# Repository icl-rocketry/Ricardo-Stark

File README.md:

# Ricardo-Stark (Engine Control Unit)

An integrated engine control unit designed to fire and control liquid bi-propellant rocket engines. Stark v1.0 has been tested in several cold flows and hotfire tests for engines ranging from 500N to 5kN. It has been flight tested on Nimbus 24 (ICLR's first liquid rocket launch) at the European Rocketry Challenge '24.

## Hardware (v1.0)
- ESP32-S3 microcontroller
- x2 Servo Channels with voltage monitor
- x1 Pyro Channel with regulated 12V
- x6 24 bit ADC channels
- microSD card logging
- x4 GPIO breakout
- CAN Bus
- USB-C Port

## Software (v1.0)
- Finite State Machine implementation
- Custom ignition sequence with propellant feed delay
- Custom valve angle configuration
- Optional remote configurability to ignition sequence

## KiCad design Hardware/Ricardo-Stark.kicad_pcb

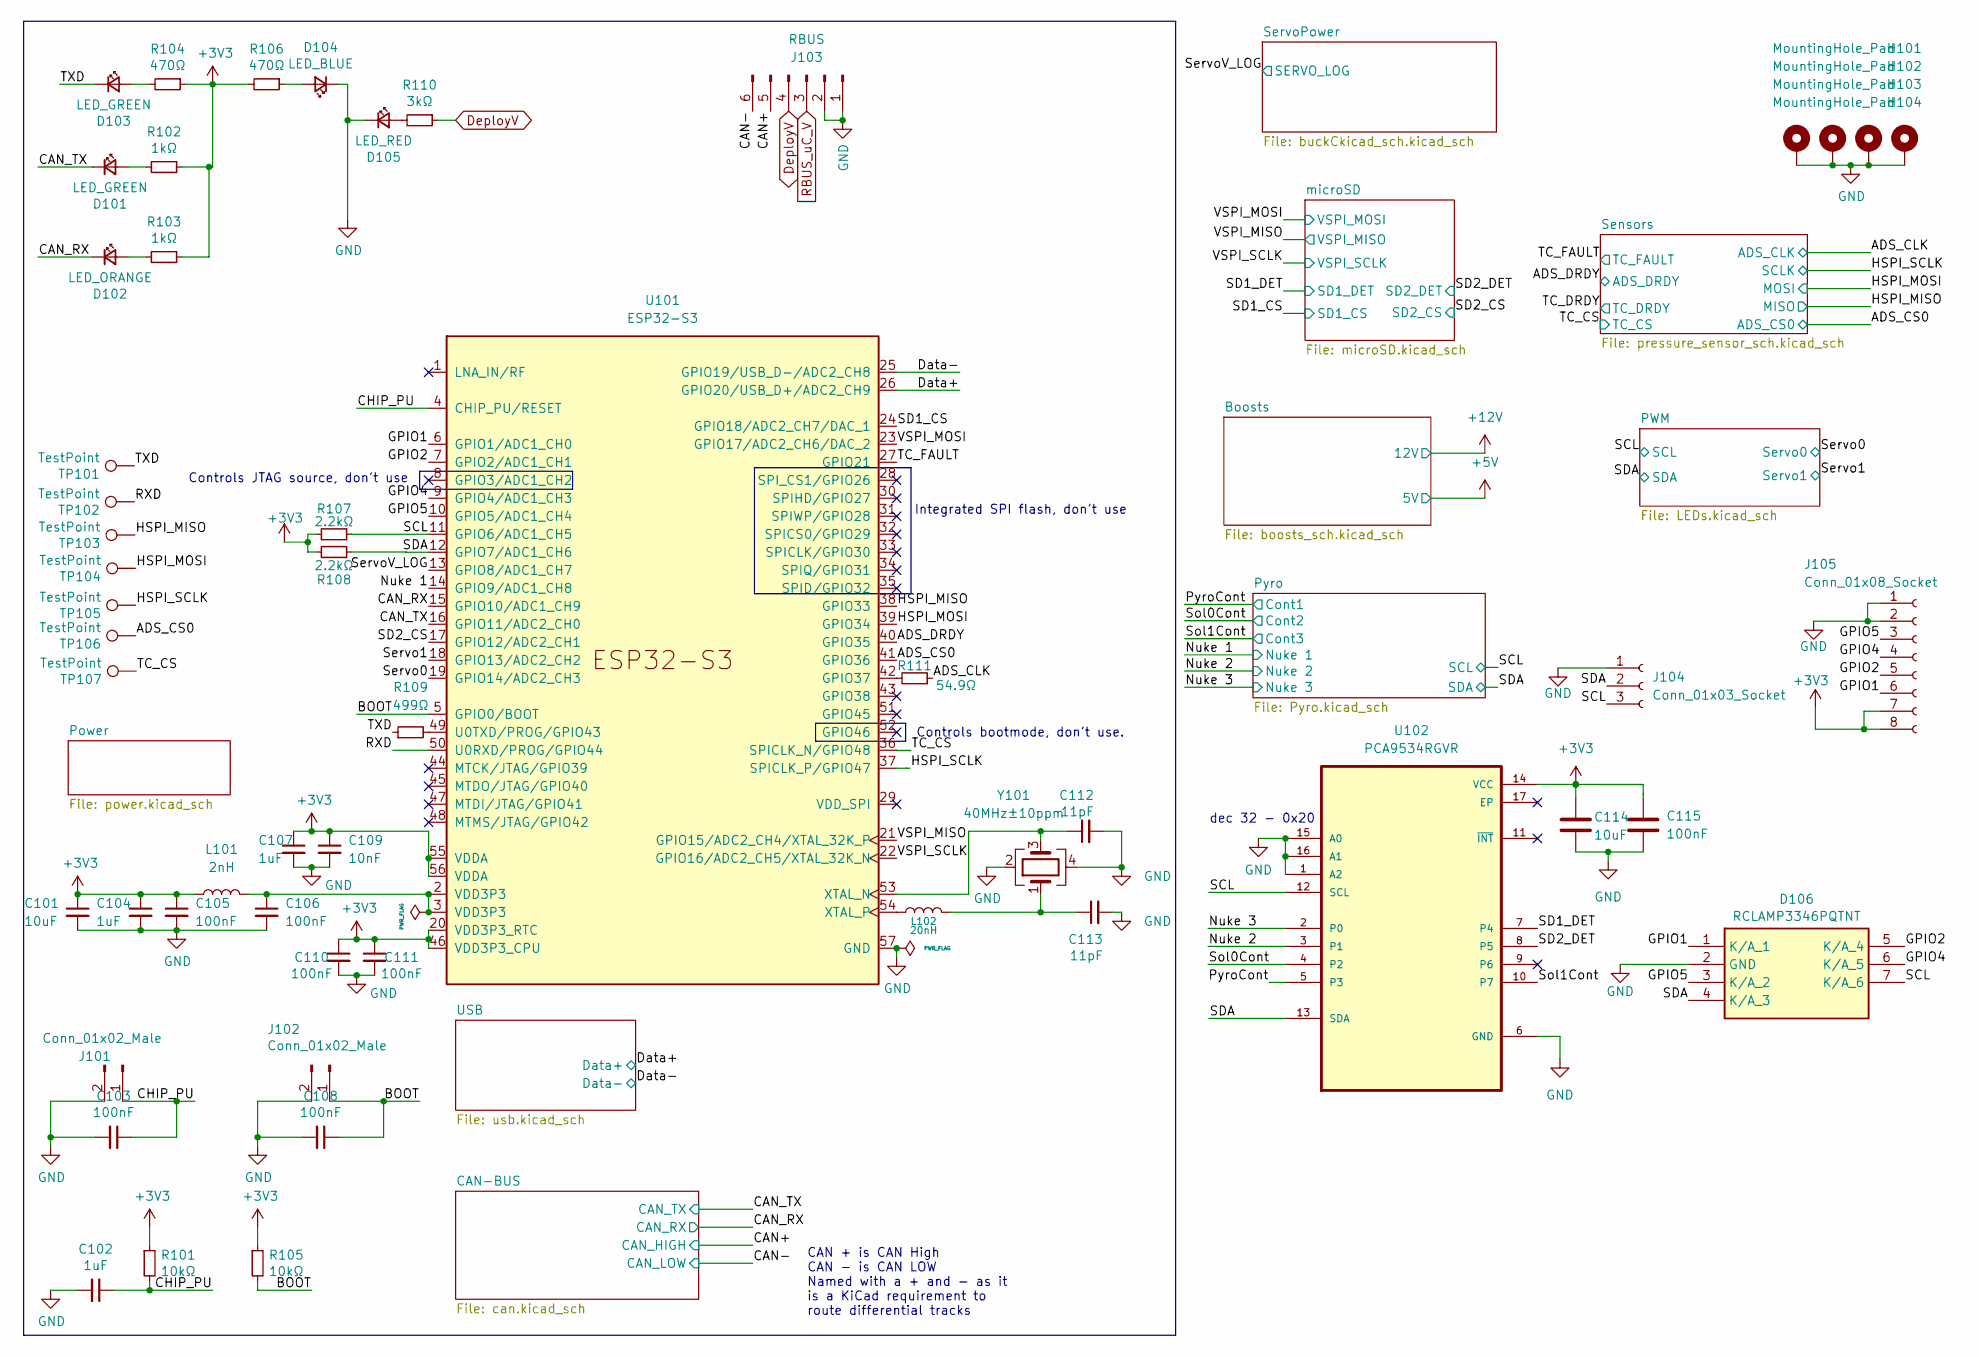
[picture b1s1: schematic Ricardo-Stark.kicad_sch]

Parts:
C101, C114: 10uF; C_0402_1005Metric
C102, C104, C107: 1uF; C_0402_1005Metric
C103, C105, C106, C108, C110, C111, C115: 100nF; C_0402_1005Metric
C109: 10nF; C_0402_1005Metric
C112, C113: 11pF; C_0402_1005Metric
D101, D103: LED_GREEN; LED_0402_1005Metric
D102: LED_ORANGE; LED_0402_1005Metric
D104: LED_BLUE; LED_0402_1005Metric
D105: LED_RED; LED_0402_1005Metric
D106: RCLAMP3346PQTNT; Mouser Part Number 947-RCLAMP3346PQTNT
H101, H102, H103, H104: MountingHole_Pad; MountingHole_3.2mm_M3_DIN965_Pad
J101, J102: Conn_01x02_Male; PinHeader_1x02_P2.54mm_Vertical
J103: RBUS; Molex_Mini-Fit_Jr_5569-06A2_2x03_P4.20mm_Horizontal
J104: Conn_01x03_Socket; PinHeader_1x03_P2.54mm_Vertical
J105: Conn_01x08_Socket; PinHeader_2x04_P2.54mm_Vertical
L101: 2nH; L_0402_1005Metric
L102: 20nH; L_0402_1005Metric
R101, R105: 10kΩ; R_0402_1005Metric
R102, R103: 1kΩ; R_0402_1005Metric
R104, R106: 470Ω; R_0402_1005Metric
R107, R108: 2.2kΩ; R_0402_1005Metric
R109: 499Ω; R_0402_1005Metric
R110: 3kΩ; R_0402_1005Metric
R111: 54.9Ω; R_0402_1005Metric
TP101, TP102, TP103, TP104, TP105, TP106, TP107: TestPoint; TestPoint_Pad_D1.0mm
U101: ESP32-S3; QFN40P700X700X90-57N
U102: PCA9534RGVR; QFN65P400X400X100-17N
Y101: 40MHz±10ppm; Crystal_SMD_2016-4Pin_2.0x1.6mm; MPN R940000171

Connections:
+3.3V: C101.1, C104.1, C105.1, C107.1, C109.1, C110.1, C111.1, C114.1, C115.1, J105.7, J105.8, L101.1, R101.1, R102.1, R103.1, R104.1, R105.1, R106.2, R107.2, R108.2, U101.20 (VDD3P3_RTC), U101.46 (VDD3P3_CPU), U101.55 (VDDA), U101.56 (VDDA), U102.14 (VCC); also elsewhere on the board
/ADS_CLK: R111.1; also elsewhere on the board
/ADS_CS0: TP106.1, U101.41 (GPIO36); also elsewhere on the board
/ADS_DRDY: U101.40 (GPIO35); also elsewhere on the board
/BOOT: C108.1, J102.1, R105.2, U101.5 (GPIO0/BOOT)
/CAN+: J103.5; also elsewhere on the board
/CAN-: J103.6; also elsewhere on the board
/CAN_RX: D102.1 (K), U101.15 (GPIO10/ADC1_CH9); also elsewhere on the board
/CAN_TX: D101.1 (K), U101.16 (GPIO11/ADC2_CH0); also elsewhere on the board
/CHIP_PU: C102.1, C103.1, J101.1, R101.2, U101.4 (CHIP_PU/RESET)
/Data+: U101.26 (GPIO20/USB_D+/ADC2_CH9); also elsewhere on the board
/Data-: U101.25 (GPIO19/USB_D-/ADC2_CH8); also elsewhere on the board
/GPIO1: D106.1 (K/A_1), J105.6, U101.6 (GPIO1/ADC1_CH0)
/GPIO2: D106.5 (K/A_4), J105.5, U101.7 (GPIO2/ADC1_CH1)
/GPIO4: D106.6 (K/A_5), J105.4, U101.9 (GPIO4/ADC1_CH3)
/GPIO5: D106.3 (K/A_2), J105.3, U101.10 (GPIO5/ADC1_CH4)
/HSPI_MISO: TP103.1, U101.38 (GPIO33); also elsewhere on the board
/HSPI_MOSI: TP104.1, U101.39 (GPIO34); also elsewhere on the board
/HSPI_SCLK: TP105.1, U101.37 (SPICLK_P/GPIO47); also elsewhere on the board
/Nuke 1: U101.14 (GPIO9/ADC1_CH8); also elsewhere on the board
/Nuke 2: U102.3 (P1); also elsewhere on the board
/Nuke 3: U102.2 (P0); also elsewhere on the board
/PyroCont: U102.5 (P3); also elsewhere on the board
/RXD: TP102.1, U101.50 (U0RXD/PROG/GPIO44)
/SCL: D106.7 (K/A_6), J104.3, R107.1, U101.11 (GPIO6/ADC1_CH5), U102.12 (SCL); also elsewhere on the board
/SD1_CS: U101.24 (GPIO18/ADC2_CH7/DAC_1); also elsewhere on the board
/SD1_DET: U102.7 (P4); also elsewhere on the board
/SD2_CS: U101.17 (GPIO12/ADC2_CH1); also elsewhere on the board
/SD2_DET: U102.8 (P5); also elsewhere on the board
/SDA: D106.4 (K/A_3), J104.2, R108.1, U101.12 (GPIO7/ADC1_CH6), U102.13 (SDA); also elsewhere on the board
/Servo0: U101.19 (GPIO14/ADC2_CH3); also elsewhere on the board
/Servo1: U101.18 (GPIO13/ADC2_CH2); also elsewhere on the board
/ServoV_LOG: U101.13 (GPIO8/ADC1_CH7); also elsewhere on the board
/Sol0Cont: U102.4 (P2); also elsewhere on the board
/Sol1Cont: U102.10 (P7); also elsewhere on the board
/TC_CS: TP107.1, U101.36 (SPICLK_N/GPIO48); also elsewhere on the board
/TC_FAULT: U101.27 (GPIO21); also elsewhere on the board
/TXD: D103.1 (K), R109.1, TP101.1
/VSPI_MISO: U101.21 (GPIO15/ADC2_CH4/XTAL_32K_P); also elsewhere on the board
/VSPI_MOSI: U101.23 (GPIO17/ADC2_CH6/DAC_2); also elsewhere on the board
/VSPI_SCLK: U101.22 (GPIO16/ADC2_CH5/XTAL_32K_N); also elsewhere on the board
DeployV: J103.4, R110.1; also elsewhere on the board
GND: C101.2, C102.2, C103.2, C104.2, C105.2, C106.2, C107.2, C108.2, C109.2, C110.2, C111.2, C112.2, C113.2, C114.2, C115.2, D104.1 (K), D105.1 (K), D106.2 (GND), H101.1, H102.1, H103.1, H104.1, J101.2, J102.2, J103.1, J103.2, J104.1, J105.1, J105.2, U101.57 (GND), U102.1 (A2), U102.6 (GND), U102.15 (A0), U102.16 (A1), Y101.2, Y101.4; also elsewhere on the board
unnamed: C106.1, L101.2, U101.2 (VDD3P3), U101.3 (VDD3P3)
unnamed: C113.1, L102.2, Y101.1
unnamed: D101.2 (A), R102.2
unnamed: D102.2 (A), R103.2
unnamed: D103.2 (A), R104.2
unnamed: D104.2 (A), R106.1
unnamed: D105.2 (A), R110.2
unnamed: R111.2, U101.42 (GPIO37)
unnamed: R109.2, U101.49 (U0TXD/PROG/GPIO43)
unnamed: C112.1, U101.53 (XTAL_N), Y101.3
unnamed: L102.1, U101.54 (XTAL_P)
RBUS_uC_V: J103.3; also elsewhere on the board

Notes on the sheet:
Controls bootmode, don't use.
CAN + is CAN High CAN - is CAN LOW Named with a + and - as it is a KiCad requirement to route differential tracks
dec 32 - 0x20
Integrated SPI flash, don't use
Controls JTAG source, don't use

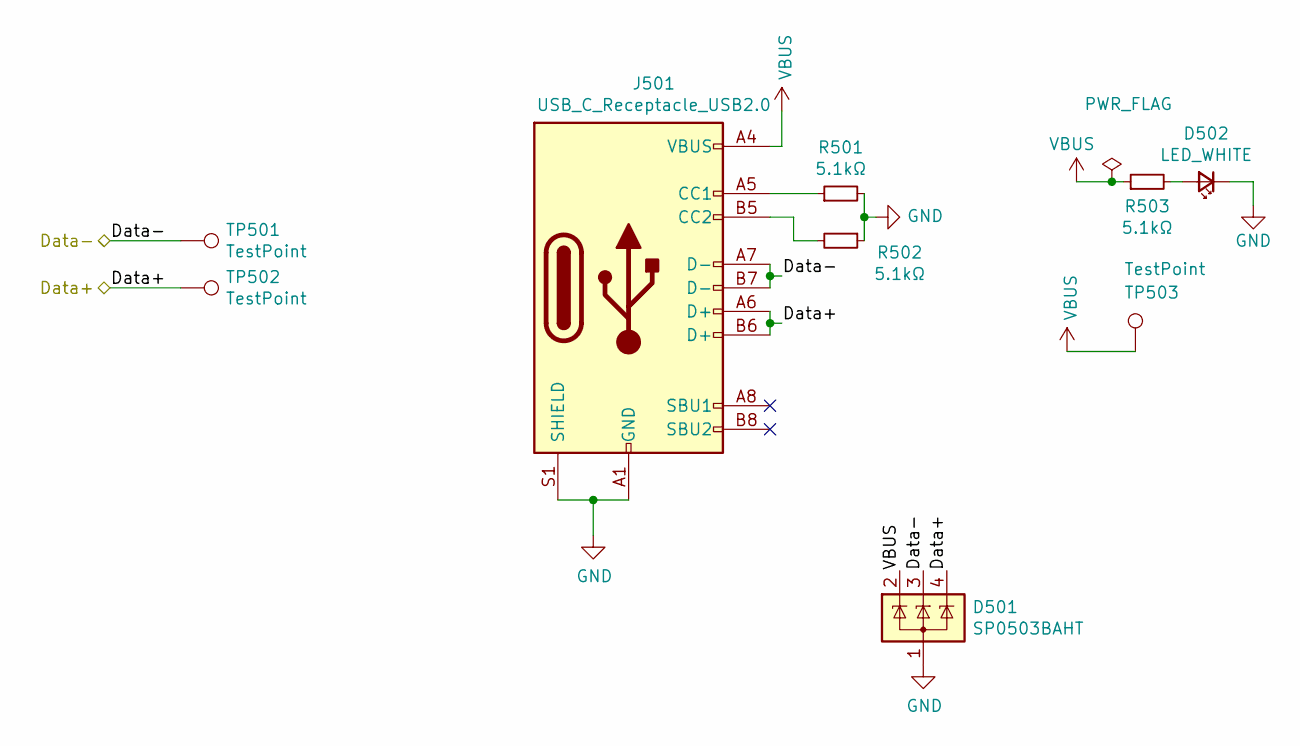
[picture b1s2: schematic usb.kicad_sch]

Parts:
D501: SP0503BAHT; SOT-143
D502: LED_WHITE; LED_0402_1005Metric
J501: USB_C_Receptacle_USB2.0; USB_C_Receptacle_Palconn_UTC16-G
R501, R502, R503: 5.1kΩ; R_0402_1005Metric
TP501, TP502: TestPoint; TestPoint_Pad_D1.0mm
TP503: TestPoint; TestPoint_Pad_D1.5mm

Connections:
/Data+: D501.4 (K), J501.A6 (D+), J501.B6 (D+), TP502.1; also elsewhere on the board
/Data-: D501.3 (K), J501.A7 (D-), J501.B7 (D-), TP501.1; also elsewhere on the board
GND: D501.1 (A), D502.1 (K), J501.A1 (GND), J501.A12 (GND), J501.B1 (GND), J501.B12 (GND), J501.S1 (SHIELD), R501.2, R502.1; also elsewhere on the board
unnamed: D502.2 (A), R503.2
unnamed: J501.A5 (CC1), R501.1
unnamed: J501.B5 (CC2), R502.2
VBUS: D501.2 (K), J501.A4 (VBUS), J501.A9 (VBUS), J501.B4 (VBUS), J501.B9 (VBUS), R503.1, TP503.1; also elsewhere on the board

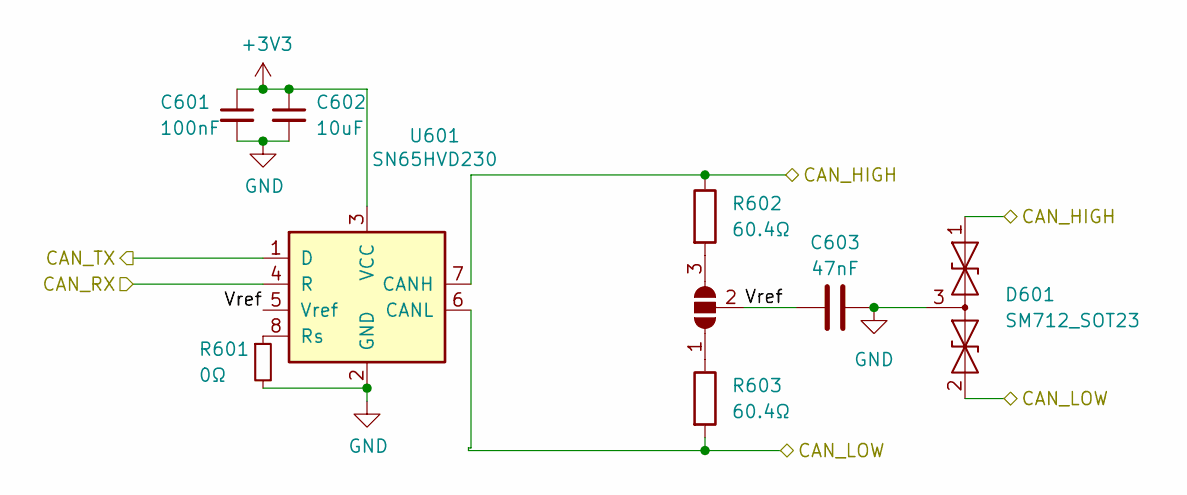
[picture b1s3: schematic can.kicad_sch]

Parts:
C601: 100nF; C_0402_1005Metric
C602: 10uF; C_0402_1005Metric
C603: 47nF; C_0402_1005Metric
D601: SM712_SOT23; SOT-23
JP601: SolderJumper_3_Open; small_3pin_SolderJP
R601: 0Ω; R_0402_1005Metric
R602, R603: 60.4Ω; R_0402_1005Metric
U601: SN65HVD230; SOIC-8_3.9x4.9mm_P1.27mm

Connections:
+3.3V: C601.1, C602.1, U601.3 (VCC); also elsewhere on the board
/CAN+: D601.1 (A1), R602.1, U601.7 (CANH); also elsewhere on the board
/CAN-: D601.2 (A2), R603.2, U601.6 (CANL); also elsewhere on the board
/CAN-BUS/Vref: C603.1, JP601.2 (C), U601.5 (Vref)
/CAN_RX: U601.4 (R); also elsewhere on the board
/CAN_TX: U601.1 (D); also elsewhere on the board
GND: C601.2, C602.2, C603.2, D601.3 (common), R601.2, U601.2 (GND); also elsewhere on the board
unnamed: JP601.1 (A), R603.1
unnamed: JP601.3 (B), R602.2
unnamed: R601.1, U601.8 (Rs)

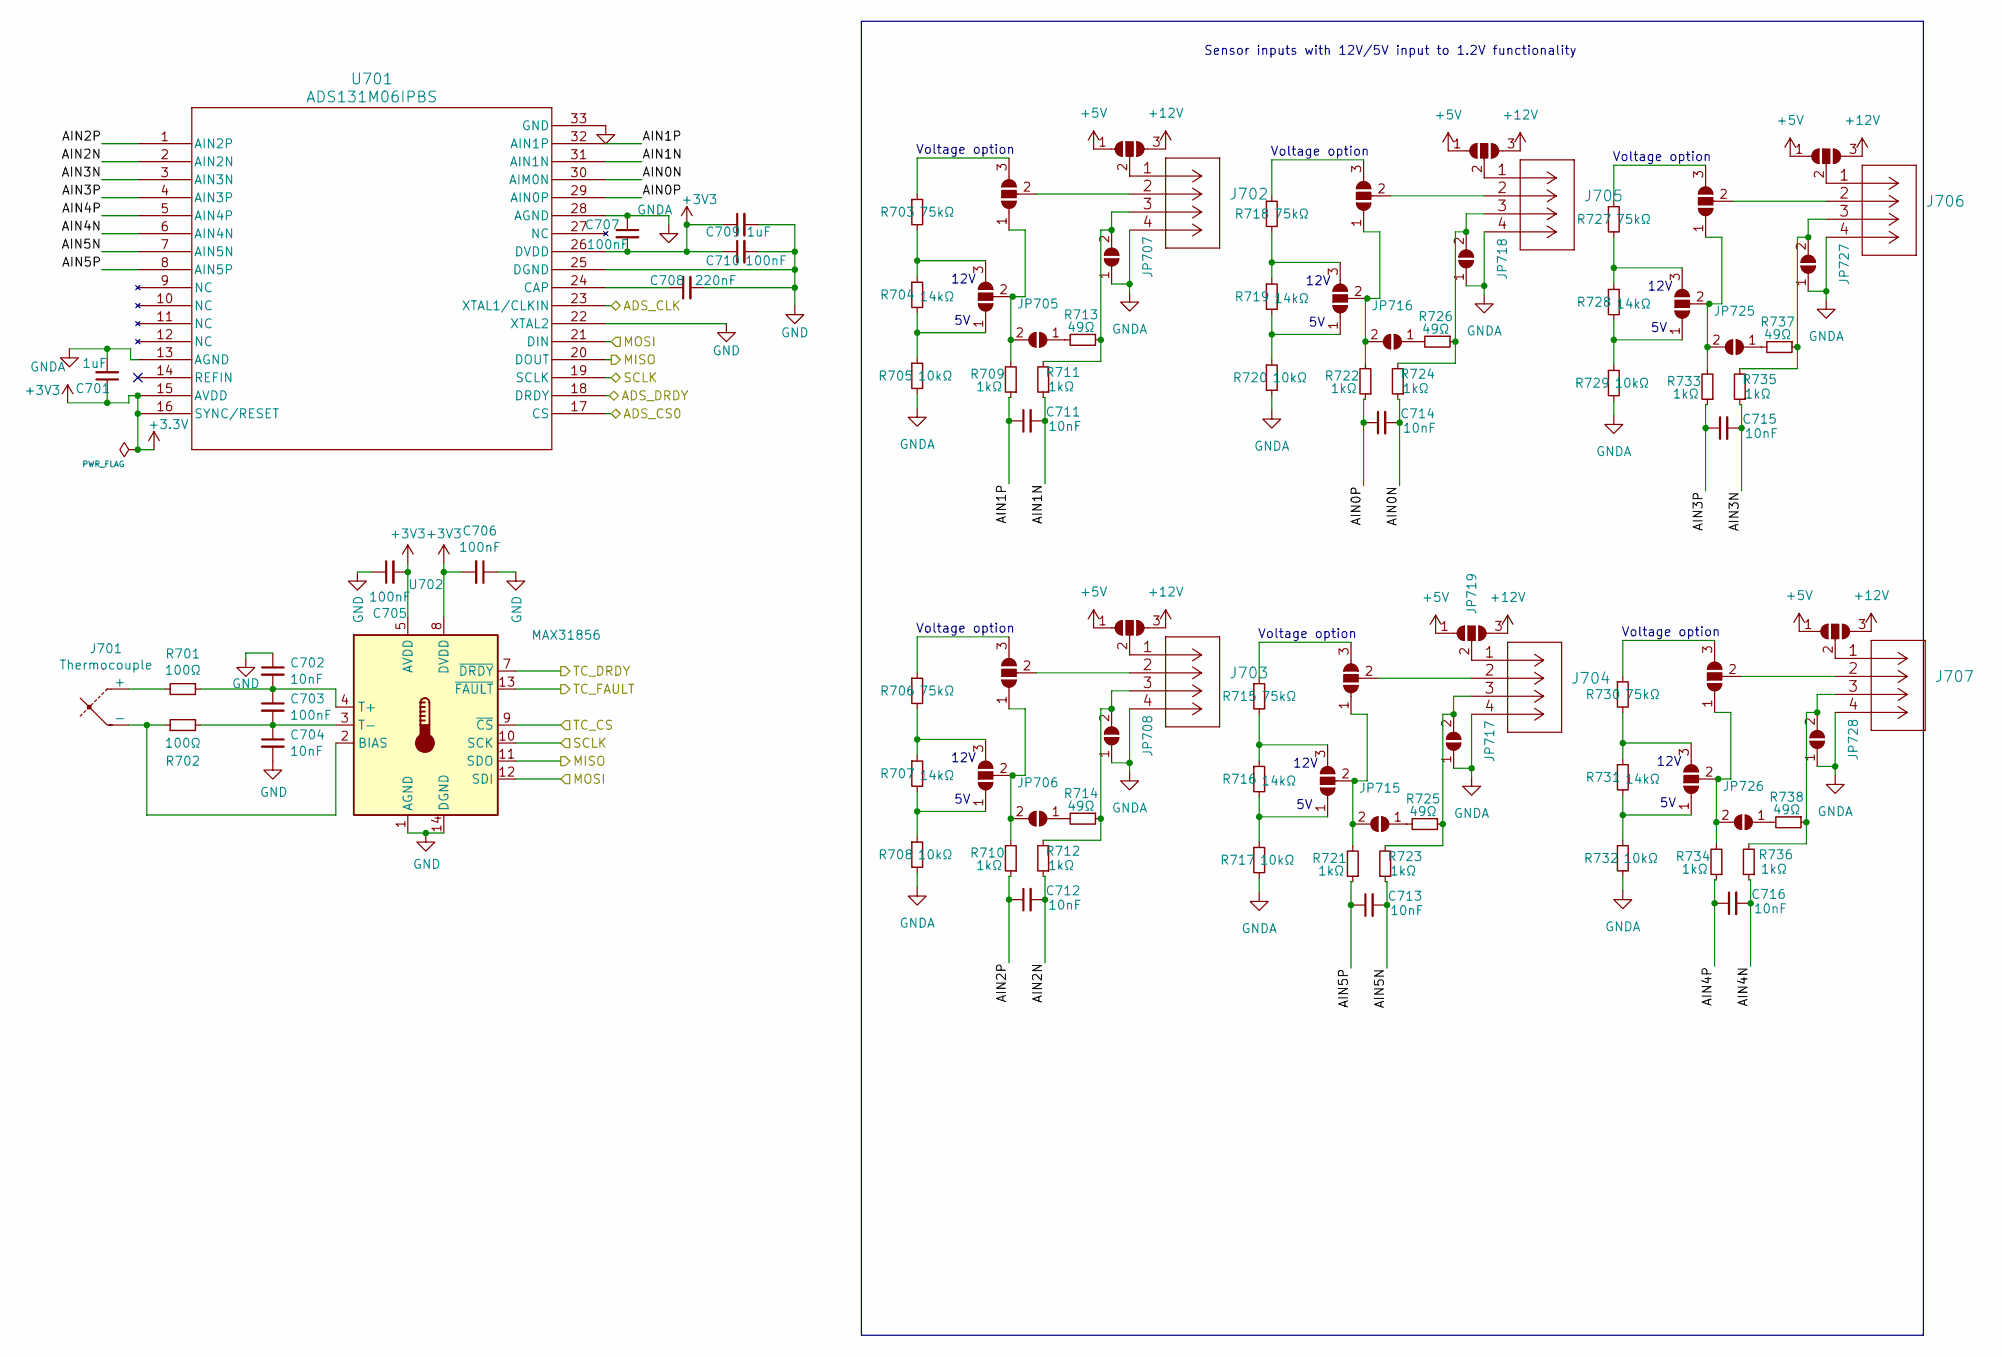
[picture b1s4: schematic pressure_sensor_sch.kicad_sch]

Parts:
C701, C709: 1uF; C_0402_1005Metric
C702, C704, C711, C712, C713, C714, C715, C716: 10nF; C_0402_1005Metric
C703, C705, C706, C707, C710: 100nF; C_0402_1005Metric
C708: 220nF; C_0402_1005Metric
J701: Thermocouple; Molex_Nano-Fit_105313-xx02_1x02_P2.50mm_Horizontal
J702, J703, J704, J705, J706, J707: 1053131104; Molex_Nano-Fit_105313-xx04_1x04_P2.50mm_Horizontal
JP701, JP702, JP703, JP704, JP709, JP710, JP711, JP712, JP713, JP714, JP719, JP720, JP721, JP722, JP723, JP724, JP729, JP730: SolderJumper_3_Open; small_3pin_SolderJP
JP705, JP706, JP707, JP708, JP715, JP716, JP717, JP718, JP725, JP726, JP727, JP728: SolderJumper_2_Open; SmallerSolderJP
R701, R702: 100Ω; R_0402_1005Metric
R703, R706, R715, R718, R727, R730: 75kΩ; R_0402_1005Metric
R704, R707, R716, R719, R728, R731: 14kΩ; R_0402_1005Metric
R705, R708, R717, R720, R729, R732: 10kΩ; R_0402_1005Metric
R709, R710, R711, R712, R721, R722, R723, R724, R733, R734, R735, R736: 1kΩ; R_0402_1005Metric
R713, R714, R725, R726, R737, R738: 49Ω; R_0402_1005Metric
U701: ADS131M06IPBS; ADS131M06IRSNR
U702: MAX31856; TSSOP-14_4.4x5mm_P0.65mm

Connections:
+3.3V: C701.1, C705.2, C706.2, C707.2, C709.1, C710.1, U701.15 (AVDD), U701.16 (SYNC/RESET), U701.26 (DVDD), U702.5 (AVDD), U702.8 (DVDD); also elsewhere on the board
+5V: JP709.1 (A), JP710.1 (A), JP719.1 (A), JP720.1 (A), JP729.1 (A), JP730.1 (A); also elsewhere on the board
+12V: JP709.3 (B), JP710.3 (B), JP719.3 (B), JP720.3 (B), JP729.3 (B), JP730.3 (B); also elsewhere on the board
/ADS_CLK: U701.23 (XTAL1/CLKIN); also elsewhere on the board
/ADS_CS0: U701.17 (CS); also elsewhere on the board
/ADS_DRDY: U701.18 (DRDY); also elsewhere on the board
/HSPI_MISO: U701.20 (DOUT), U702.11 (SDO); also elsewhere on the board
/HSPI_MOSI: U701.21 (DIN), U702.12 (SDI); also elsewhere on the board
/HSPI_SCLK: U701.19 (SCLK), U702.10 (SCK); also elsewhere on the board
/Sensors/AIN0N: C714.2, R724.1, U701.30 (AIM0N)
/Sensors/AIN0P: C714.1, R722.1, U701.29 (AIN0P)
/Sensors/AIN1N: C711.2, R711.1, U701.31 (AIN1N)
/Sensors/AIN1P: C711.1, R709.1, U701.32 (AIN1P)
/Sensors/AIN2N: C712.2, R712.1, U701.2 (AIN2N)
/Sensors/AIN2P: C712.1, R710.1, U701.1 (AIN2P)
/Sensors/AIN3N: C715.2, R735.1, U701.3 (AIN3N)
/Sensors/AIN3P: C715.1, R733.1, U701.4 (AIN3P)
/Sensors/AIN4N: C716.2, R736.1, U701.6 (AIN4N)
/Sensors/AIN4P: C716.1, R734.1, U701.5 (AIN4P)
/Sensors/AIN5N: C713.2, R723.1, U701.7 (AIN5N)
/Sensors/AIN5P: C713.1, R721.1, U701.8 (AIN5P)
/TC_CS: U702.9 (~CS); also elsewhere on the board
/TC_DRDY: U702.7 (~DRDY)
/TC_FAULT: U702.13 (~FAULT); also elsewhere on the board
GND: C701.2, C702.1, C704.2, C705.1, C706.1, C707.1, C708.2, C709.2, C710.2, J702.4, J703.4, J704.4, J705.4, J706.4, J707.4, JP707.1 (A), JP708.1 (A), JP717.1 (A), JP718.1 (A), JP727.1 (A), JP728.1 (A), R705.2, R708.2, R717.2, R720.2, R729.2, R732.2, U701.13 (AGND), U701.22 (XTAL2), U701.25 (DGND), U701.28 (AGND), U701.33 (GND), U702.1 (AGND), U702.14 (DGND); also elsewhere on the board
unnamed: J701.1 (+), R701.2
unnamed: J701.2 (-), R702.1, U702.2 (BIAS)
unnamed: JP701.1 (A), R704.2, R705.1
unnamed: JP701.3 (B), R703.2, R704.1
unnamed: JP701.2 (C), JP703.1 (A), JP705.2 (B), R709.2
unnamed: JP702.1 (A), R707.2, R708.1
unnamed: JP702.3 (B), R706.2, R707.1
unnamed: JP702.2 (C), JP704.1 (A), JP706.2 (B), R710.2
unnamed: JP703.3 (B), R703.1
unnamed: J702.2, JP703.2 (C)
unnamed: JP704.3 (B), R706.1
unnamed: J703.2, JP704.2 (C)
unnamed: JP705.1 (A), R713.2
unnamed: JP706.1 (A), R714.2
unnamed: J702.3, JP707.2 (B), R711.2, R713.1
unnamed: J703.3, JP708.2 (B), R712.2, R714.1
unnamed: J702.1, JP709.2 (C)
unnamed: J703.1, JP710.2 (C)
unnamed: JP711.1 (A), R716.2, R717.1
unnamed: JP711.3 (B), R715.2, R716.1
unnamed: JP711.2 (C), JP713.1 (A), JP715.2 (B), R721.2
unnamed: JP712.1 (A), R719.2, R720.1
unnamed: JP712.3 (B), R718.2, R719.1
unnamed: JP712.2 (C), JP714.1 (A), JP716.2 (B), R722.2
unnamed: JP713.3 (B), R715.1
unnamed: J704.2, JP713.2 (C)
unnamed: JP714.3 (B), R718.1
unnamed: J705.2, JP714.2 (C)
unnamed: JP715.1 (A), R725.2
unnamed: JP716.1 (A), R726.2
unnamed: J704.3, JP717.2 (B), R723.2, R725.1
unnamed: J705.3, JP718.2 (B), R724.2, R726.1
unnamed: J704.1, JP719.2 (C)
unnamed: J705.1, JP720.2 (C)
unnamed: JP721.1 (A), R728.2, R729.1
unnamed: JP721.3 (B), R727.2, R728.1
unnamed: JP721.2 (C), JP723.1 (A), JP725.2 (B), R733.2
unnamed: JP722.1 (A), R731.2, R732.1
unnamed: JP722.3 (B), R730.2, R731.1
unnamed: JP722.2 (C), JP724.1 (A), JP726.2 (B), R734.2
unnamed: JP723.3 (B), R727.1
unnamed: J706.2, JP723.2 (C)
unnamed: JP724.3 (B), R730.1
unnamed: J707.2, JP724.2 (C)
unnamed: JP725.1 (A), R737.2
unnamed: JP726.1 (A), R738.2
unnamed: J706.3, JP727.2 (B), R735.2, R737.1
unnamed: J707.3, JP728.2 (B), R736.2, R738.1
unnamed: J706.1, JP729.2 (C)
unnamed: J707.1, JP730.2 (C)
unnamed: C708.1, U701.24 (CAP)
unnamed: C702.2, C703.1, R701.1, U702.4 (T+)
unnamed: C703.2, C704.1, R702.2, U702.3 (T-)

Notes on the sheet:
Voltage option
Sensor inputs with 12V/5V input to 1.2V functionality
12V

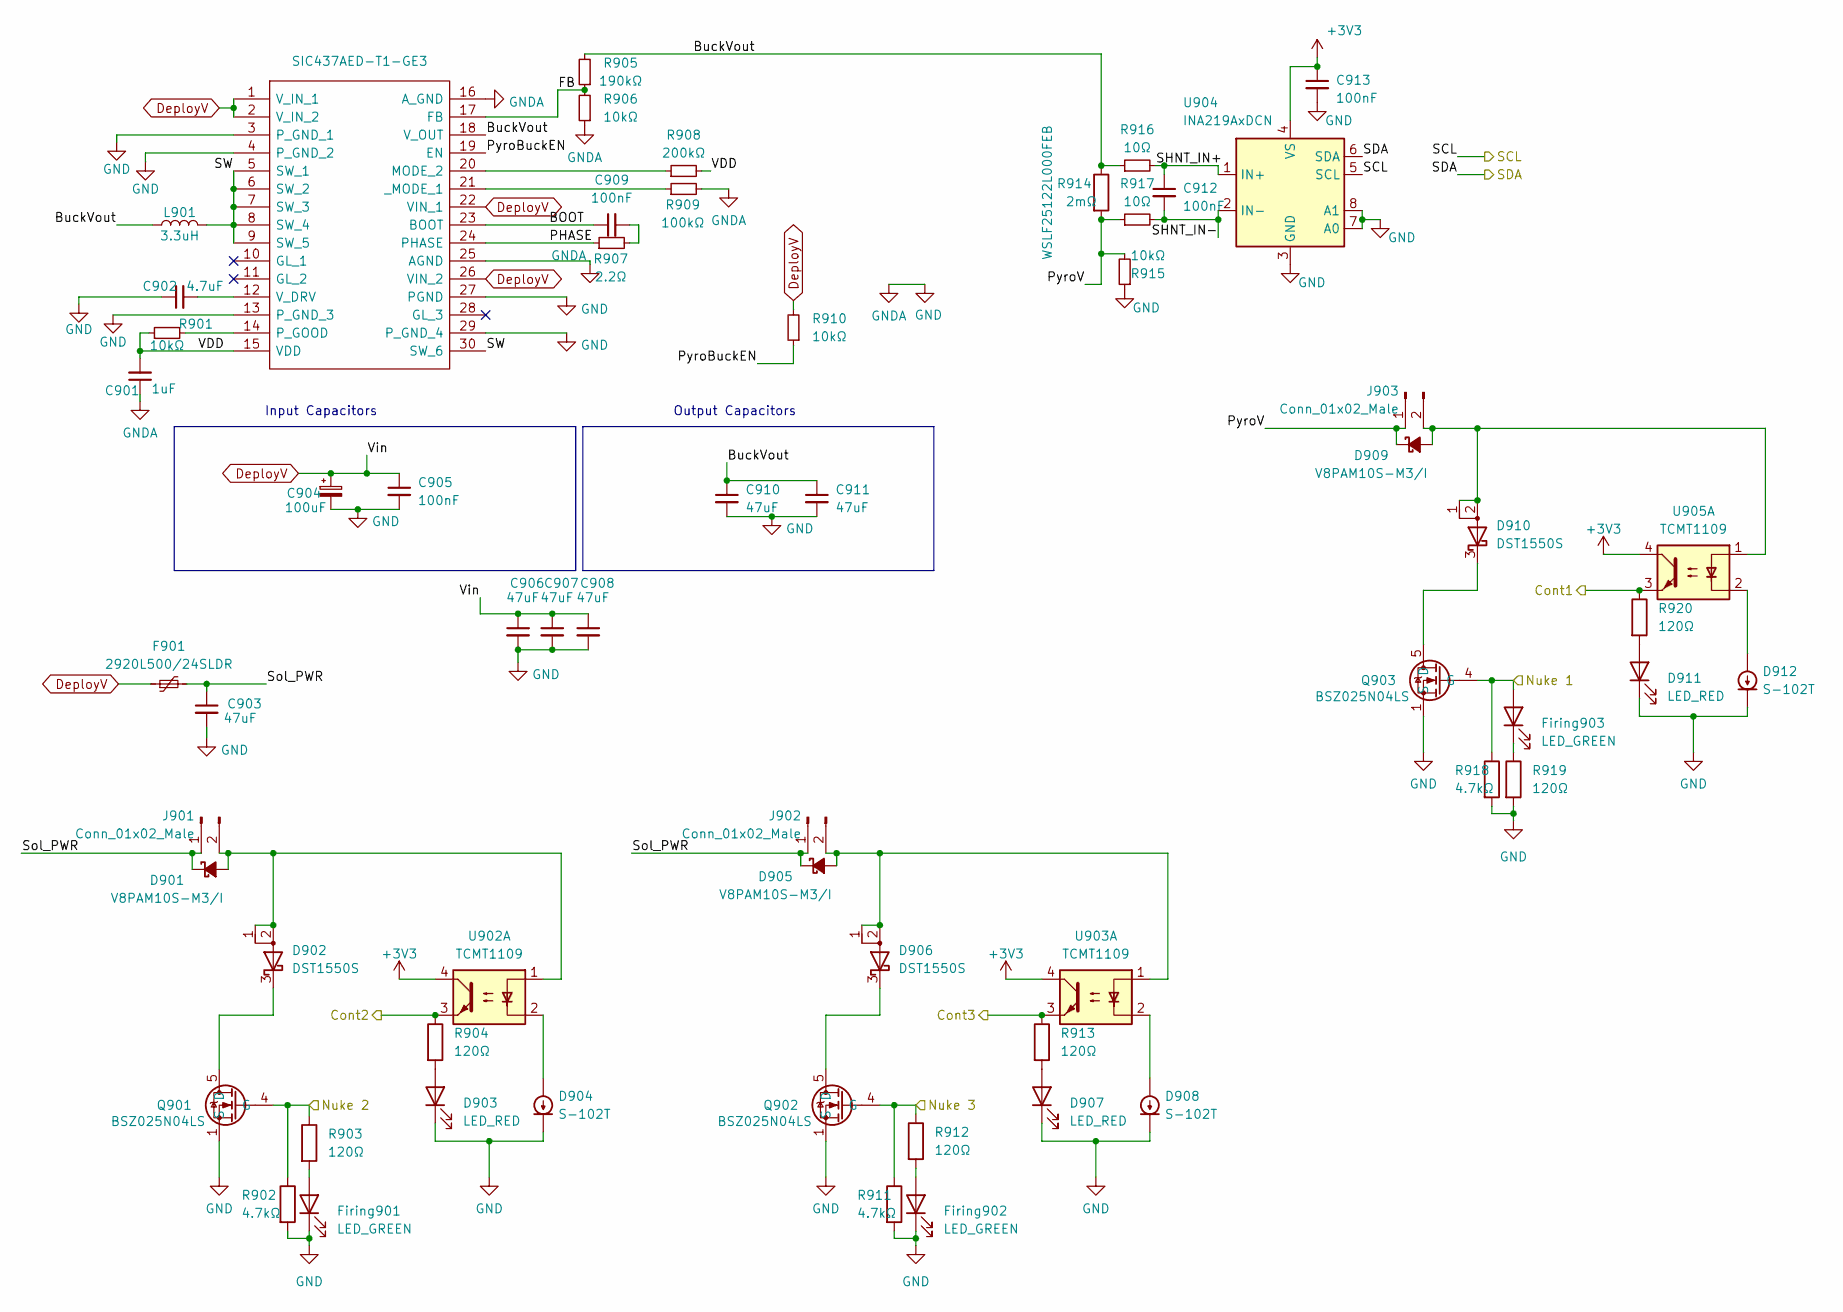
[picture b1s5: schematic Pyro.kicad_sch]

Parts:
C901: 1uF; C_0402_1005Metric
C902: 4.7uF; C_0402_1005Metric
C903, C906, C907, C908, C910, C911: 47uF; C_1206_3216Metric
C904: 100uF; CP_EIA-7360-38_Kemet-E
C905, C909, C912, C913: 100nF; C_0402_1005Metric
D901, D905, D909: V8PAM10S-M3/I; V8PAM10SM3I
D902, D906, D910: DST1550S; TO-277B
D903, D907, D911: LED_RED; LED_0603_1608Metric
D904, D908, D912: S-102T; SODFL3516X70N
F901: 2920L500/24SLDR; Fuse_2920_7451Metric
Firing901, Firing902, Firing903: LED_GREEN; LED_0402_1005Metric
J901, J902, J903: Conn_01x02_Male; Molex_Nano-Fit_105313-xx02_1x02_P2.50mm_Horizontal
L901: 3.3uH; WE-XHMI_7070
Q901, Q902, Q903: BSZ025N04LS; Manufacturer_Part_Number BSZ025N04LS; Mouser Part Number 726-BSZ025N04LS
R901, R906, R910, R915: 10kΩ; R_0402_1005Metric
R902, R911, R918: 4.7kΩ; R_0402_1005Metric
R903, R912, R919: 120Ω; R_0402_1005Metric
R904, R913, R920: 120Ω; R_0603_1608Metric
R905: 190kΩ; R_0603_1608Metric_Pad0.98x0.95mm_HandSolder
R907: 2.2Ω; R_0402_1005Metric
R908: 200kΩ; R_0402_1005Metric
R909: 100kΩ; R_0402_1005Metric
R914: 2mΩ; R_2512_6332Metric_Pad1.40x3.35mm_HandSolder; MPN WSLF25122L000FEB
R916, R917: 10Ω; R_0402_1005Metric
U901: SIC437AED-T1-GE3; SiC437BEDT1GE3; Manufacturer_Part_Number SiC437BED-T1-GE3; Mouser Part Number 78-SIC437BED-T1-GE3
U902, U903, U905: TCMT1109; SOP-4_4.4x2.6mm_P1.27mm
U904: INA219AxDCN; SOT-23-8

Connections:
+3.3V: C913.1, U902.4, U903.4, U904.4 (VS), U905.4; also elsewhere on the board
/Nuke 1: Firing903.2 (A), Q903.4 (G), R918.1; also elsewhere on the board
/Nuke 2: Q901.4 (G), R902.1, R903.1; also elsewhere on the board
/Nuke 3: Q902.4 (G), R911.1, R912.1; also elsewhere on the board
/Pyro/BOOT: C909.1, U901.23 (BOOT)
/Pyro/BuckVout: C910.1, C911.1, L901.1, R905.2, R914.1, R916.1, U901.18 (V_OUT)
/Pyro/FB: R905.1, R906.2, U901.17 (FB)
/Pyro/PHASE: R907.1, U901.24 (PHASE)
/Pyro/PyroBuckEN: R910.1, U901.19 (EN)
/Pyro/PyroV: D909.1 (K), J903.1, R914.2, R915.2, R917.1
/Pyro/SHNT_IN+: C912.1, R916.2, U904.1 (IN+)
/Pyro/SHNT_IN-: C912.2, R917.2, U904.2 (IN-)
/Pyro/SW: L901.2, U901.5 (SW_1), U901.6 (SW_2), U901.7 (SW_3), U901.8 (SW_4), U901.9 (SW_5), U901.30 (SW_6)
/Pyro/Sol_PWR: C903.1, D901.1 (K), D905.1 (K), F901.2, J901.1, J902.1
/Pyro/VDD: C901.2, R901.1, R908.2, U901.15 (VDD)
/PyroCont: R920.1, U905.3; also elsewhere on the board
/SCL: U904.5 (SCL); also elsewhere on the board
/SDA: U904.6 (SDA); also elsewhere on the board
/Sol0Cont: R904.1, U902.3; also elsewhere on the board
/Sol1Cont: R913.1, U903.3; also elsewhere on the board
DeployV: C904.1, C905.1, C906.1, C907.1, C908.1, F901.1, R910.2, U901.1 (V_IN_1), U901.2 (V_IN_2), U901.22 (VIN_1), U901.26 (VIN_2); also elsewhere on the board
GND: C901.1, C902.1, C903.2, C904.2, C905.2, C906.2, C907.2, C908.2, C910.2, C911.2, C913.2, D903.1 (K), D904.1 (K), D907.1 (K), D908.1 (K), D911.1 (K), D912.1 (K), Firing901.1 (K), Firing902.1 (K), Q901.1 (S), Q901.2 (S), Q901.3 (S), Q901.A1 (S), Q902.1 (S), Q902.2 (S), Q902.3 (S), Q902.A1 (S), Q903.1 (S), Q903.2 (S), Q903.3 (S), Q903.A1 (S), R902.2, R906.1, R909.2, R911.2, R915.1, R918.2, R919.2, U901.3 (P_GND_1), U901.4 (P_GND_2), U901.13 (P_GND_3), U901.16 (A_GND), U901.25 (AGND), U901.27 (PGND), U901.29 (P_GND_4), U904.3 (GND), U904.7 (A0), U904.8 (A1); also elsewhere on the board
unnamed: C909.2, R907.2
unnamed: D901.2 (A), D902.1 (A), D902.2 (A), J901.2, U902.1
unnamed: D902.3 (K), Q901.5 (D), Q901.6 (D), Q901.7 (D), Q901.8 (D), Q901.A5 (D)
unnamed: D903.2 (A), R904.2
unnamed: D904.2 (A), U902.2
unnamed: D905.2 (A), D906.1 (A), D906.2 (A), J902.2, U903.1
unnamed: D906.3 (K), Q902.5 (D), Q902.6 (D), Q902.7 (D), Q902.8 (D), Q902.A5 (D)
unnamed: D907.2 (A), R913.2
unnamed: D908.2 (A), U903.2
unnamed: D909.2 (A), D910.1 (A), D910.2 (A), J903.2, U905.1
unnamed: D910.3 (K), Q903.5 (D), Q903.6 (D), Q903.7 (D), Q903.8 (D), Q903.A5 (D)
unnamed: D911.2 (A), R920.2
unnamed: D912.2 (A), U905.2
unnamed: Firing901.2 (A), R903.2
unnamed: Firing902.2 (A), R912.2
unnamed: Firing903.1 (K), R919.1
unnamed: R908.1, U901.20 (MODE_2)
unnamed: R901.2, U901.14 (P_GOOD)
unnamed: C902.2, U901.12 (V_DRV)
unnamed: R909.1, U901.21 (_MODE_1)

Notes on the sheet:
Input Capacitors
Output Capacitors

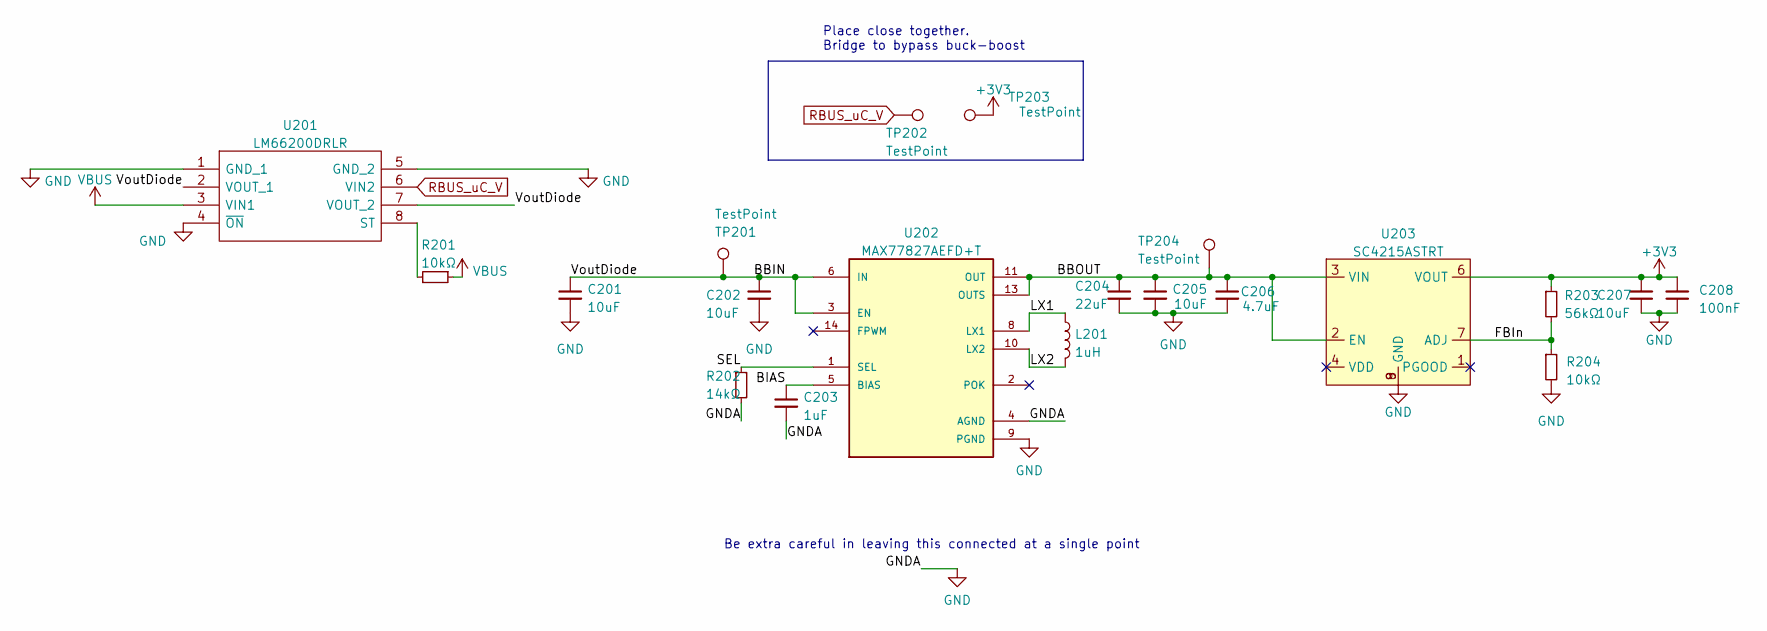
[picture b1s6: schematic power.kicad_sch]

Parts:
C201, C205, C207: 10uF; C_0402_1005Metric
C202: 10uF; C_0603_1608Metric
C203: 1uF; C_0402_1005Metric
C204: 22uF; C_0603_1608Metric
C206: 4.7uF; C_0402_1005Metric
C208: 100nF; C_0402_1005Metric
L201: 1uH; L_0805_2012Metric
R201, R204: 10kΩ; R_0402_1005Metric
R202: 14kΩ; R_0402_1005Metric
R203: 56kΩ; R_0402_1005Metric
TP201, TP202, TP203, TP204: TestPoint; TestPoint_Pad_D1.5mm
U201: LM66200DRLR; SOTFL50P160X60-8N; Manufacturer_Part_Number LM66200DRLR; Mouser Part Number 595-LM66200DRLR
U202: MAX77827AEFD+T; CONV_MAX77827AEFD+T; PARTREV B
U203: SC4215ASTRT; SOIC127P599X175-9N

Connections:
+3.3V: C207.2, C208.2, R203.1, TP203.1, U203.6 (VOUT); also elsewhere on the board
/Power/BBIN: C201.1, C202.1, TP201.1, U201.2 (VOUT_1), U201.7 (VOUT_2), U202.3 (EN), U202.6 (IN)
/Power/BBOUT: C204.1, C205.1, C206.1, TP204.1, U202.11 (OUT), U202.13 (OUTS), U203.2 (EN), U203.3 (VIN)
/Power/BIAS: C203.1, U202.5 (BIAS)
/Power/FBIn: R203.2, R204.1, U203.7 (ADJ)
/Power/LX1: L201.1, U202.8 (LX1)
/Power/LX2: L201.2, U202.10 (LX2)
/Power/SEL: R202.1, U202.1 (SEL)
GND: C201.2, C202.2, C203.2, C204.2, C205.2, C206.2, C207.1, C208.1, R202.2, R204.2, U201.1 (GND_1), U201.4 (~ON), U201.5 (GND_2), U202.4 (AGND), U202.9 (PGND), U203.8 (GND), U203.9 (GND); also elsewhere on the board
unnamed: R201.2, U201.8 (ST)
RBUS_uC_V: TP202.1, U201.6 (VIN2); also elsewhere on the board
VBUS: R201.1, U201.3 (VIN1); also elsewhere on the board

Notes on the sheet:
Place close together. Bridge to bypass buck-boost
Be extra careful in leaving this connected at a single point

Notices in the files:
parts and their libraries:
Copyright 2021 Accelerated Designs. All rights reserved.
